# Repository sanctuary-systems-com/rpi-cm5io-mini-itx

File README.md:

# rpi-cm5io-mini-itx
A mini ITX board with PCIe x16 based on the Raspberry Pi Comput Module 5 IO board

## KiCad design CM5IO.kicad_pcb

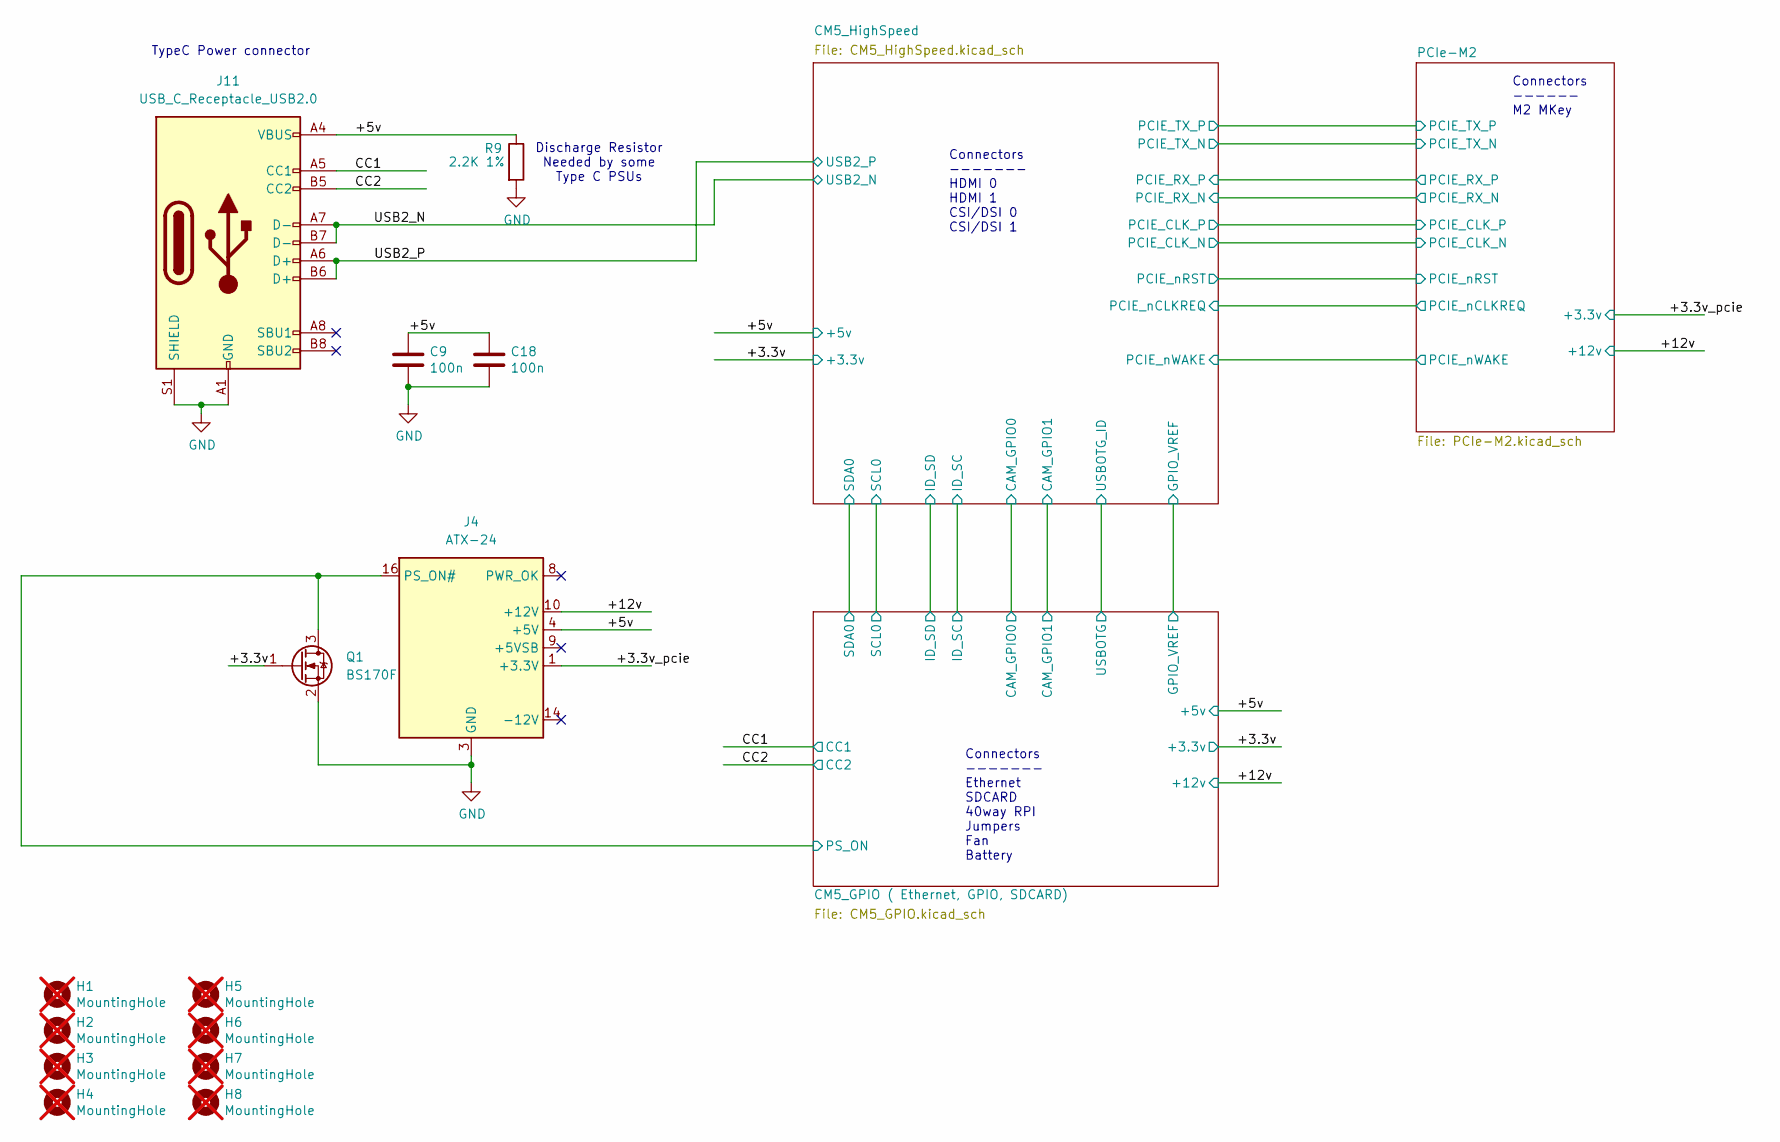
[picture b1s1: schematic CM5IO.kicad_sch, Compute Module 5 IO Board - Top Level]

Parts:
C9, C18: 100n; C_0402_1005Metric; Part Description 0.1uF 10% 16V Ceramic Capacitor X7R 040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; LCSC C92753
H1, H6, H7, H8: MountingHole; atx_mountinghole; Part Description M2.5 mounting hole; not fitted
H2, H3, H4, H5: MountingHole; MountingHole_2.7mm_M2.5_DIN965; Part Description M2.5 mounting hole; not fitted
J4: ATX-24; Molex_Mini-Fit_Jr_5566-24A_2x12_P4.20mm_Vertical; LCSC C114088
J11: USB_C_Receptacle_USB2.0; USB_C_Receptacle_GCT_USB4105-xx-A_16P_TopMnt_Horizontal; Part Description USBC USB2 data and power connector; LCSC C5184243
Q1: BS170F; SOT-23; LCSC C16197299
R9: 2.2K 1%; R_0402_1005Metric; Part Description Resistor 2.2K M1005 1% 63mW; LCSC C328314

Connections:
/+3.3v: Q1.1 (G); also elsewhere on the board
/+3.3v_pcie: J4.1 (+3.3V), J4.2 (+3.3V), J4.12 (+3.3V), J4.13 (+3.3V); also elsewhere on the board
/+5v: C9.1, C18.1, J4.4 (+5V), J4.6 (+5V), J4.21 (+5V), J4.22 (+5V), J4.23 (+5V), J11.A4 (VBUS), J11.A9 (VBUS), J11.B4 (VBUS), J11.B9 (VBUS), R9.1; also elsewhere on the board
/+12v: J4.10 (+12V), J4.11 (+12V); also elsewhere on the board
/CC1: J11.A5 (CC1); also elsewhere on the board
/CC2: J11.B5 (CC2); also elsewhere on the board
/CM5_GPIO ( Ethernet, GPIO, SDCARD)/PS_ON: J4.16 (PS_ON#), Q1.3 (D); also elsewhere on the board
/USB2_N: J11.A7 (D-), J11.B7 (D-); also elsewhere on the board
/USB2_P: J11.A6 (D+), J11.B6 (D+); also elsewhere on the board
GND: C9.2, C18.2, J4.3 (GND), J4.5 (GND), J4.7 (GND), J4.15 (GND), J4.17 (GND), J4.18 (GND), J4.19 (GND), J4.24 (GND), J11.A1 (GND), J11.A12 (GND), J11.B1 (GND), J11.B12 (GND), J11.S1 (SHIELD), Q1.2 (S), R9.2; also elsewhere on the board

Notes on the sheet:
Connectors ------- Ethernet SDCARD 40way RPI Jumpers Fan Battery
Connectors ------ M2 MKey
Discharge Resistor Needed by some Type C PSUs
TypeC Power connector
Connectors ------- HDMI 0 HDMI 1 CSI/DSI 0 CSI/DSI 1

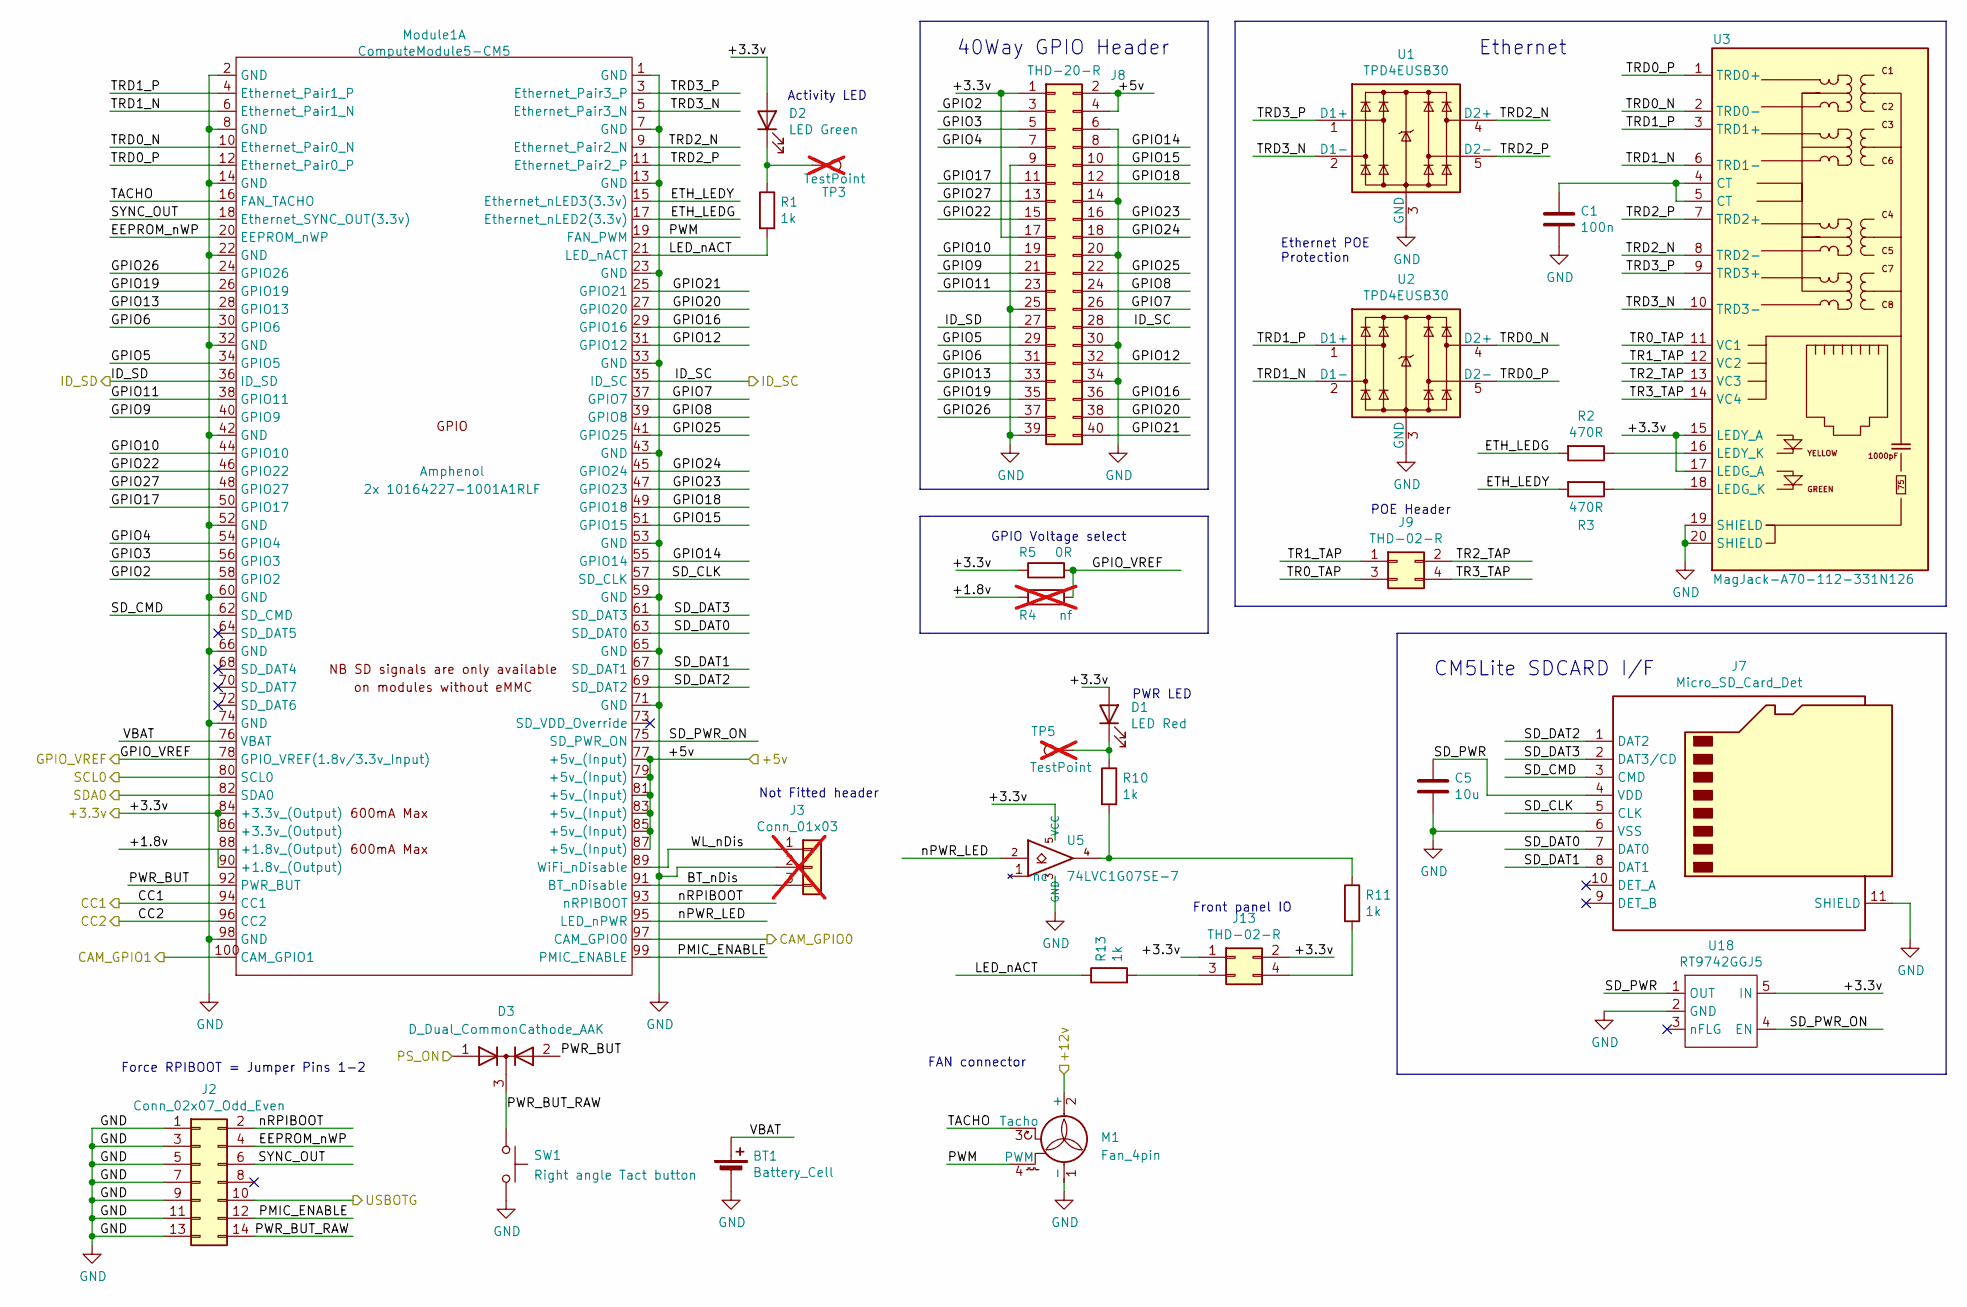
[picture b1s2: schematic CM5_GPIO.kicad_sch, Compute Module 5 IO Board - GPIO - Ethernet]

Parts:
BT1: Battery_Cell; BatteryHolder_Keystone_3034_1x20mm; Part Description Battery Retainer Coin, 20.0mm 1 Cell SM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; LCSC C5213768
C1: 100n; C_0402_1005Metric; Part Description 0.1uF 10% 16V Ceramic Capacitor X7R 040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; LCSC C92753
C5: 10u; C_0805_2012Metric; Part Description 10uF 10% 10V Ceramic Capacitor X7R 0805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; LCSC C117956
D1: LED Red; LED_0603_1608Metric; Part Description Red 620nm LED Indication - Discrete 2.2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; LCSC C125114
D2: LED Green; LED_0603_1608Metric; Part Description Green 572nm LED Indication - Discrete 2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; LCSC C125113
D3: D_Dual_CommonCathode_AAK; SOT-23; mpn BAT54-05; LCSC C37704
J2: Conn_02x07_Odd_Even; PinHeader_2x07_P2.54mm_Vertical; Part Description PinHeader_2x07_P2.54mm_Vertical; LCSC C492424
J3: Conn_01x03; PinHeader_1x03_P2.54mm_Vertical; Part Description 3pin 0.1" connector; not fitted
J7: Micro_SD_Card_Det; SDCARD_MOLEX_503398-1892; Part Description 9 (8 + 1) Position Card Connector micro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; LCSC C428492
J8: THD-20-R; PinHeader_2x20_P2.54mm_Vertical; Part Description PinHeader_2x20_P2.54mm_Vertical; LCSC C124383
J9, J13: THD-02-R; PinHeader_2x02_P2.54mm_Vertical; Part Description PinHeader_2x02_P2.54mm_Vertical; LCSC C492419
M1: Fan_4pin; FanPinHeader_1x04_P2.54mm_Vertical; mpn 0470531000; LCSC C240840
Module1: ComputeModule5-CM5; Raspberry-Pi-5-Compute-Module; Part Description 100 Position Connector Receptacle, Cent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; LCSC C19089295
R1, R10, R11, R13: 1k; R_0402_1005Metric; Part Description Resistor 1K M1005 1% 63mW; LCSC C131360
R2, R3: 470R; R_0402_1005Metric; Part Description Resistor 470R M1005 1% 63mW; LCSC C352415
R4: nf; R_0805_2012Metric_Pad1.20x1.40mm_HandSolder; not fitted
R5: 0R; R_0805_2012Metric_Pad1.20x1.40mm_HandSolder; Part Description Resistor 0R M2012 5%; LCSC C17477
SW1: Right angle Tact button; SW_Tactile_SPST_Angled_PTS645Vx58-2LFS; Part Description Right angle through hole Tact switch; LCSC C127680
TP3, TP5: TestPoint; TestPoint_Pad_2.0x2.0mm; Part Description Test point; not fitted
U1, U2: TPD4EUSB30; USON-10_2.5x1.0mm_P0.5mm; Part Description Quad TVS diode for high speed signals (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; LCSC C913227
U3: MagJack-A70-112-331N126; TRJG0926HENL; Part Description Gigabit Ethernet Magjack
U5: 74LVC1G07SE-7; SOT-353_SC-70-5; Part Description Buffer, Non-Inverting 1 Element 1 Bit p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; LCSC C67531
U18: RT9742GGJ5; SOT-23-5; Part Description Power Switch/Driver 1:1 N-Channel 1A TS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; LCSC C250547

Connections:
/+3.3v: D1.2 (A), D2.2 (A), J8.1, J8.17, J13.1, J13.2, Module1.84 (+3.3v_(Output)), Module1.86 (+3.3v_(Output)), R5.1, U3.15 (LEDY_A), U3.17 (LEDG_A), U5.5 (VCC), U18.5 (IN); also elsewhere on the board
/+5v: J8.2, J8.4, Module1.77 (+5v_(Input)), Module1.79 (+5v_(Input)), Module1.81 (+5v_(Input)), Module1.83 (+5v_(Input)), Module1.85 (+5v_(Input)), Module1.87 (+5v_(Input)); also elsewhere on the board
/+12v: M1.2 (+); also elsewhere on the board
/CC1: Module1.94 (CC1); also elsewhere on the board
/CC2: Module1.96 (CC2); also elsewhere on the board
/CM5_GPIO ( Ethernet, GPIO, SDCARD)/+1.8v: Module1.88 (+1.8v_(Output)), Module1.90 (+1.8v_(Output)), R4.1
/CM5_GPIO ( Ethernet, GPIO, SDCARD)/BT_nDis: J3.3, Module1.91 (BT_nDisable)
/CM5_GPIO ( Ethernet, GPIO, SDCARD)/CAM_GPIO0: Module1.97 (CAM_GPIO0); also elsewhere on the board
/CM5_GPIO ( Ethernet, GPIO, SDCARD)/CAM_GPIO1: Module1.100 (CAM_GPIO1); also elsewhere on the board
/CM5_GPIO ( Ethernet, GPIO, SDCARD)/EEPROM_nWP: J2.4, Module1.20 (EEPROM_nWP)
/CM5_GPIO ( Ethernet, GPIO, SDCARD)/ETH_LEDG: Module1.17 (Ethernet_nLED2(3.3v)), R2.2
/CM5_GPIO ( Ethernet, GPIO, SDCARD)/ETH_LEDY: Module1.15 (Ethernet_nLED3(3.3v)), R3.2
/CM5_GPIO ( Ethernet, GPIO, SDCARD)/GPIO2: J8.3, Module1.58 (GPIO2)
/CM5_GPIO ( Ethernet, GPIO, SDCARD)/GPIO3: J8.5, Module1.56 (GPIO3)
/CM5_GPIO ( Ethernet, GPIO, SDCARD)/GPIO4: J8.7, Module1.54 (GPIO4)
/CM5_GPIO ( Ethernet, GPIO, SDCARD)/GPIO5: J8.29, Module1.34 (GPIO5)
/CM5_GPIO ( Ethernet, GPIO, SDCARD)/GPIO6: J8.31, Module1.30 (GPIO6)
/CM5_GPIO ( Ethernet, GPIO, SDCARD)/GPIO7: J8.26, Module1.37 (GPIO7)
/CM5_GPIO ( Ethernet, GPIO, SDCARD)/GPIO8: J8.24, Module1.39 (GPIO8)
/CM5_GPIO ( Ethernet, GPIO, SDCARD)/GPIO9: J8.21, Module1.40 (GPIO9)
/CM5_GPIO ( Ethernet, GPIO, SDCARD)/GPIO10: J8.19, Module1.44 (GPIO10)
/CM5_GPIO ( Ethernet, GPIO, SDCARD)/GPIO11: J8.23, Module1.38 (GPIO11)
/CM5_GPIO ( Ethernet, GPIO, SDCARD)/GPIO12: J8.32, Module1.31 (GPIO12)
/CM5_GPIO ( Ethernet, GPIO, SDCARD)/GPIO13: J8.33, Module1.28 (GPIO13)
/CM5_GPIO ( Ethernet, GPIO, SDCARD)/GPIO14: J8.8, Module1.55 (GPIO14)
/CM5_GPIO ( Ethernet, GPIO, SDCARD)/GPIO15: J8.10, Module1.51 (GPIO15)
/CM5_GPIO ( Ethernet, GPIO, SDCARD)/GPIO16: J8.36, Module1.29 (GPIO16)
/CM5_GPIO ( Ethernet, GPIO, SDCARD)/GPIO17: J8.11, Module1.50 (GPIO17)
/CM5_GPIO ( Ethernet, GPIO, SDCARD)/GPIO18: J8.12, Module1.49 (GPIO18)
/CM5_GPIO ( Ethernet, GPIO, SDCARD)/GPIO19: J8.35, Module1.26 (GPIO19)
/CM5_GPIO ( Ethernet, GPIO, SDCARD)/GPIO20: J8.38, Module1.27 (GPIO20)
/CM5_GPIO ( Ethernet, GPIO, SDCARD)/GPIO21: J8.40, Module1.25 (GPIO21)
/CM5_GPIO ( Ethernet, GPIO, SDCARD)/GPIO22: J8.15, Module1.46 (GPIO22)
/CM5_GPIO ( Ethernet, GPIO, SDCARD)/GPIO23: J8.16, Module1.47 (GPIO23)
/CM5_GPIO ( Ethernet, GPIO, SDCARD)/GPIO24: J8.18, Module1.45 (GPIO24)
/CM5_GPIO ( Ethernet, GPIO, SDCARD)/GPIO25: J8.22, Module1.41 (GPIO25)
/CM5_GPIO ( Ethernet, GPIO, SDCARD)/GPIO26: J8.37, Module1.24 (GPIO26)
/CM5_GPIO ( Ethernet, GPIO, SDCARD)/GPIO27: J8.13, Module1.48 (GPIO27)
/CM5_GPIO ( Ethernet, GPIO, SDCARD)/GPIO_VREF: Module1.78 (GPIO_VREF(1.8v/3.3v_Input)), R4.2, R5.2; also elsewhere on the board
/CM5_GPIO ( Ethernet, GPIO, SDCARD)/ID_SC: J8.28, Module1.35 (ID_SC); also elsewhere on the board
/CM5_GPIO ( Ethernet, GPIO, SDCARD)/ID_SD: J8.27, Module1.36 (ID_SD); also elsewhere on the board
/CM5_GPIO ( Ethernet, GPIO, SDCARD)/LED_nACT: Module1.21 (LED_nACT), R1.2, R13.1
/CM5_GPIO ( Ethernet, GPIO, SDCARD)/PMIC_ENABLE: J2.12, Module1.99 (PMIC_ENABLE)
/CM5_GPIO ( Ethernet, GPIO, SDCARD)/PS_ON: D3.1 (A); also elsewhere on the board
/CM5_GPIO ( Ethernet, GPIO, SDCARD)/PWM: M1.4 (PWM), Module1.19 (FAN_PWM)
/CM5_GPIO ( Ethernet, GPIO, SDCARD)/PWR_BUT: D3.2 (A), Module1.92 (PWR_BUT)
/CM5_GPIO ( Ethernet, GPIO, SDCARD)/PWR_BUT_RAW: D3.3 (K), J2.14, SW1.1
/CM5_GPIO ( Ethernet, GPIO, SDCARD)/SD_CLK: J7.5 (CLK), Module1.57 (SD_CLK)
/CM5_GPIO ( Ethernet, GPIO, SDCARD)/SD_CMD: J7.3 (CMD), Module1.62 (SD_CMD)
/CM5_GPIO ( Ethernet, GPIO, SDCARD)/SD_DAT0: J7.7 (DAT0), Module1.63 (SD_DAT0)
/CM5_GPIO ( Ethernet, GPIO, SDCARD)/SD_DAT1: J7.8 (DAT1), Module1.67 (SD_DAT1)
/CM5_GPIO ( Ethernet, GPIO, SDCARD)/SD_DAT2: J7.1 (DAT2), Module1.69 (SD_DAT2)
/CM5_GPIO ( Ethernet, GPIO, SDCARD)/SD_DAT3: J7.2 (DAT3/CD), Module1.61 (SD_DAT3)
/CM5_GPIO ( Ethernet, GPIO, SDCARD)/SD_PWR: C5.1, J7.4 (VDD), U18.1 (OUT)
/CM5_GPIO ( Ethernet, GPIO, SDCARD)/SD_PWR_ON: Module1.75 (SD_PWR_ON), U18.4 (EN)
/CM5_GPIO ( Ethernet, GPIO, SDCARD)/SYNC_OUT: J2.6, Module1.18 (Ethernet_SYNC_OUT(3.3v))
/CM5_GPIO ( Ethernet, GPIO, SDCARD)/TACHO: M1.3 (Tacho), Module1.16 (FAN_TACHO)
/CM5_GPIO ( Ethernet, GPIO, SDCARD)/TR0_TAP: J9.3, U3.11 (VC1)
/CM5_GPIO ( Ethernet, GPIO, SDCARD)/TR1_TAP: J9.1, U3.12 (VC2)
/CM5_GPIO ( Ethernet, GPIO, SDCARD)/TR2_TAP: J9.2, U3.13 (VC3)
/CM5_GPIO ( Ethernet, GPIO, SDCARD)/TR3_TAP: J9.4, U3.14 (VC4)
/CM5_GPIO ( Ethernet, GPIO, SDCARD)/TRD0_N: Module1.10 (Ethernet_Pair0_N), U2.4 (D2+), U2.7, U3.2 (TRD0-)
/CM5_GPIO ( Ethernet, GPIO, SDCARD)/TRD0_P: Module1.12 (Ethernet_Pair0_P), U2.5 (D2-), U2.6, U3.1 (TRD0+)
/CM5_GPIO ( Ethernet, GPIO, SDCARD)/TRD1_N: Module1.6 (Ethernet_Pair1_N), U2.2 (D1-), U2.9, U3.6 (TRD1-)
/CM5_GPIO ( Ethernet, GPIO, SDCARD)/TRD1_P: Module1.4 (Ethernet_Pair1_P), U2.1 (D1+), U2.10, U3.3 (TRD1+)
/CM5_GPIO ( Ethernet, GPIO, SDCARD)/TRD2_N: Module1.9 (Ethernet_Pair2_N), U1.4 (D2+), U1.7, U3.8 (TRD2-)
/CM5_GPIO ( Ethernet, GPIO, SDCARD)/TRD2_P: Module1.11 (Ethernet_Pair2_P), U1.5 (D2-), U1.6, U3.7 (TRD2+)
/CM5_GPIO ( Ethernet, GPIO, SDCARD)/TRD3_N: Module1.5 (Ethernet_Pair3_N), U1.2 (D1-), U1.9, U3.10 (TRD3-)
/CM5_GPIO ( Ethernet, GPIO, SDCARD)/TRD3_P: Module1.3 (Ethernet_Pair3_P), U1.1 (D1+), U1.10, U3.9 (TRD3+)
/CM5_GPIO ( Ethernet, GPIO, SDCARD)/USBOTG: J2.10; also elsewhere on the board
/CM5_GPIO ( Ethernet, GPIO, SDCARD)/VBAT: BT1.1 (+), Module1.76 (VBAT)
/CM5_GPIO ( Ethernet, GPIO, SDCARD)/WL_nDis: J3.1, Module1.89 (WiFi_nDisable)
/CM5_GPIO ( Ethernet, GPIO, SDCARD)/nPWR_LED: Module1.95 (LED_nPWR), U5.2
/CM5_GPIO ( Ethernet, GPIO, SDCARD)/nRPIBOOT: J2.2, Module1.93 (nRPIBOOT)
/CM5_HighSpeed/SCL0: Module1.80 (SCL0); also elsewhere on the board
/CM5_HighSpeed/SDA0: Module1.82 (SDA0); also elsewhere on the board
GND: BT1.2 (-), C1.2, C5.2, J2.1, J2.3, J2.5, J2.7, J2.9, J2.11, J2.13, J3.2, J7.6 (VSS), J7.11 (SHIELD), J8.6, J8.9, J8.14, J8.20, J8.25, J8.30, J8.34, J8.39, M1.1 (-), Module1.1 (GND), Module1.2 (GND), Module1.7 (GND), Module1.8 (GND), Module1.13 (GND), Module1.14 (GND), Module1.22 (GND), Module1.23 (GND), Module1.32 (GND), Module1.33 (GND), Module1.42 (GND), Module1.43 (GND), Module1.52 (GND), Module1.53 (GND), Module1.59 (GND), Module1.60 (GND), Module1.65 (GND), Module1.66 (GND), Module1.71 (GND), Module1.74 (GND), Module1.98 (GND), SW1.2, U1.3 (GND), U1.8 (GND), U2.3 (GND), U2.8 (GND), U3.19 (SHIELD), U3.20 (SHIELD), U5.3 (GND), U18.2 (GND); also elsewhere on the board
unnamed: C1.1, U3.4 (CT), U3.5 (CT)
unnamed: D1.1 (K), R10.1, TP5.1
unnamed: D2.1 (K), R1.1, TP3.1
unnamed: J13.3, R13.2
unnamed: J13.4, R11.2
unnamed: R10.2, R11.1, U5.4
unnamed: R3.1, U3.18 (LEDG_K)
unnamed: R2.1, U3.16 (LEDY_K)

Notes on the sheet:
40Way GPIO Header
Activity LED
FAN connector
Ethernet POE Protection
Front panel IO
GPIO Voltage select
Not Fitted header
POE Header
Force RPIBOOT = Jumper Pins 1-2
PWR LED
Ethernet
CM5Lite SDCARD I/F

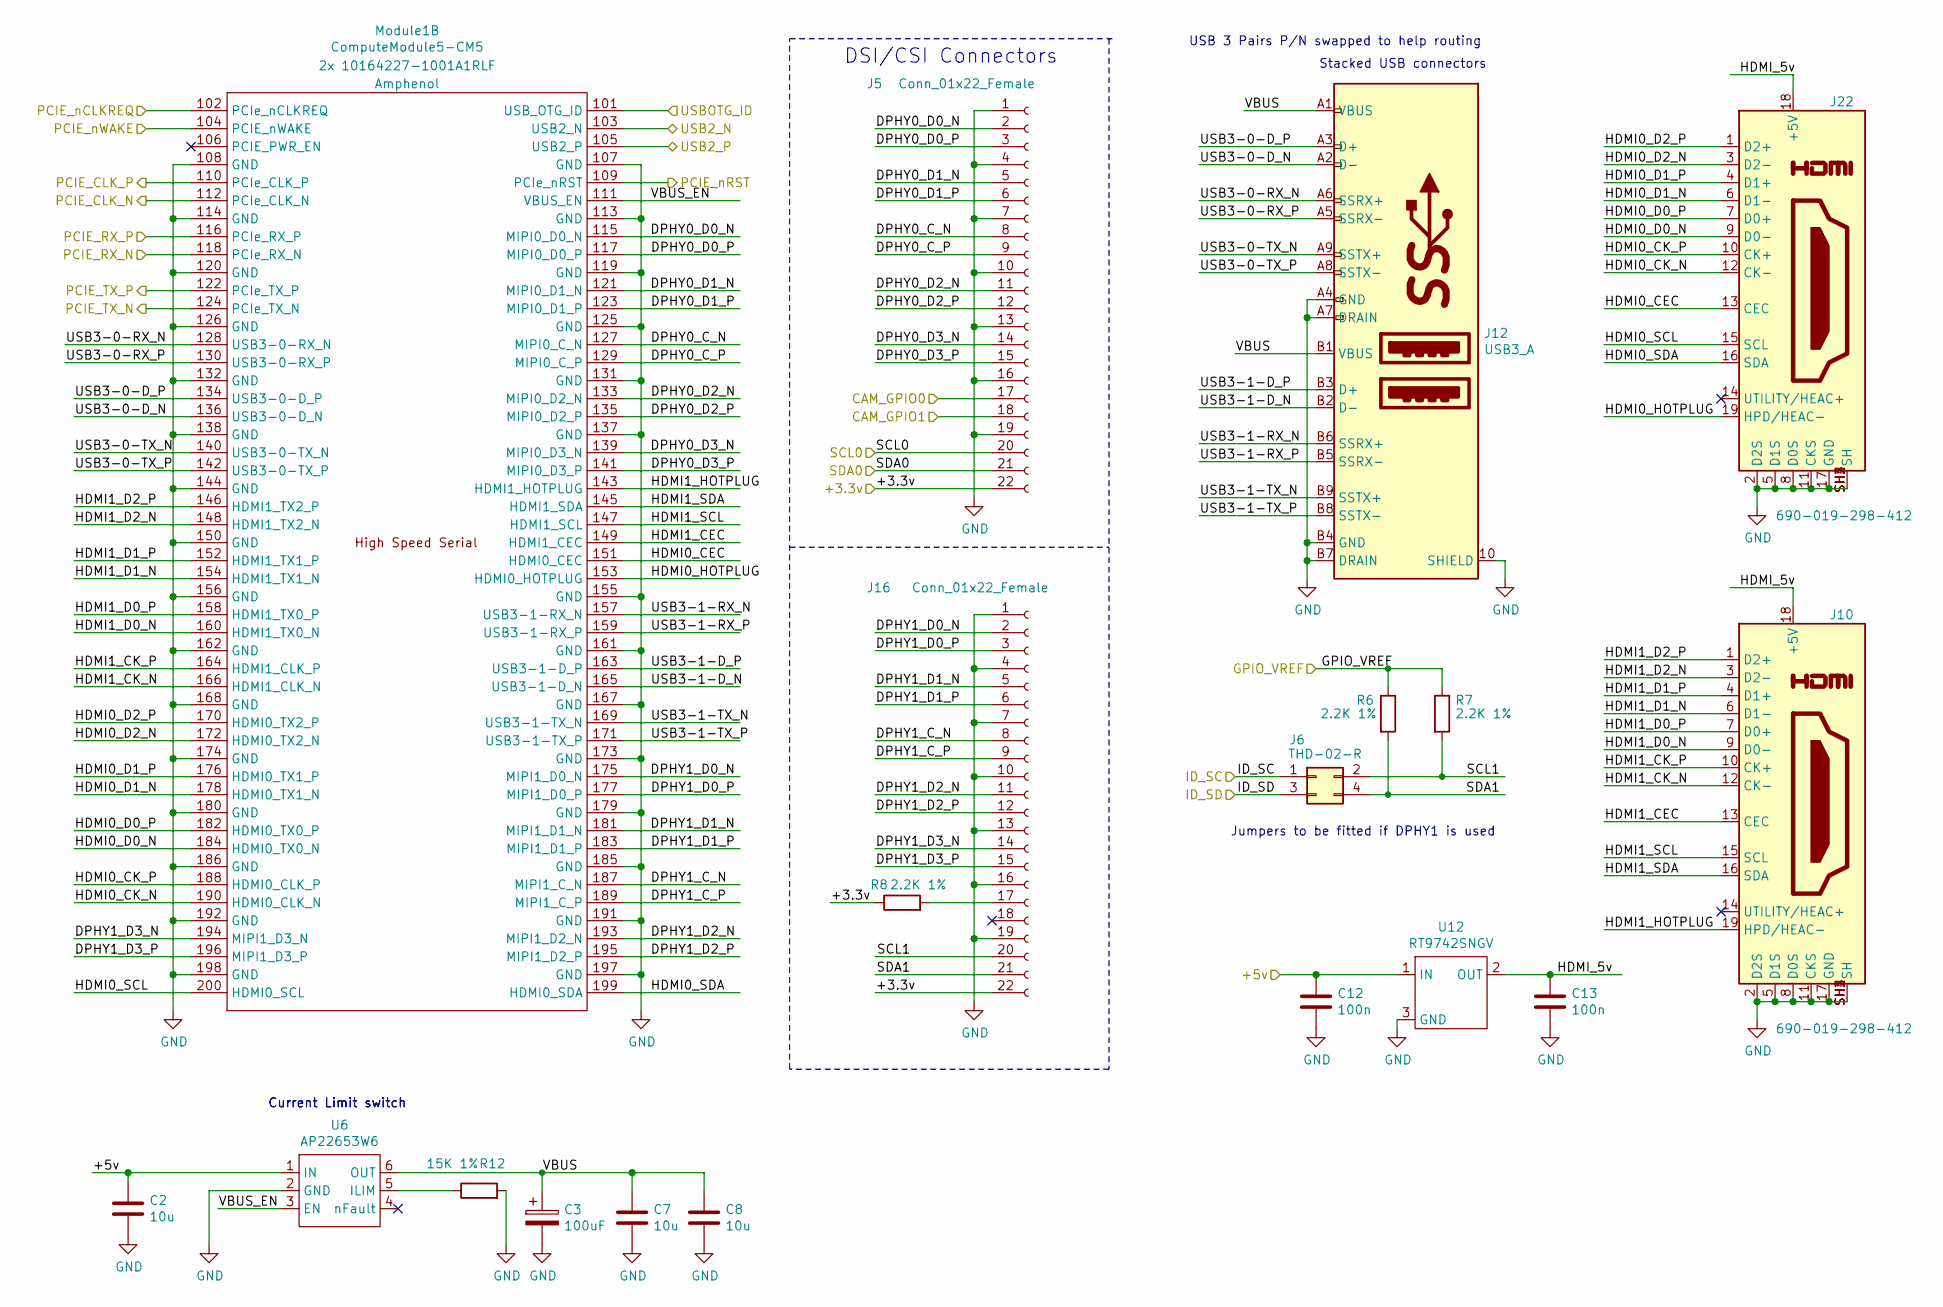
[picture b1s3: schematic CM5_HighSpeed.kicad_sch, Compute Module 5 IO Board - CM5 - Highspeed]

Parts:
C2, C7, C8: 10u; C_0805_2012Metric; Part Description 10uF 10% 10V Ceramic Capacitor X7R 0805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; LCSC C117956
C3: 100uF; CP_EIA-7343-31_Kemet-D; Part Description Capacitor, SP-Cap, 100u, 6.3V, 15mR ESR; LCSC C189619
C12, C13: 100n; C_0402_1005Metric; Part Description 0.1uF 10% 16V Ceramic Capacitor X7R 040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; LCSC C92753
J5, J16: Conn_01x22_Female; Hirose_FH12-22S-0.5SH_1x22-1MP_P0.50mm_Horizontal; Part Description 22 Position FFC, FPC Connector Contacts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; LCSC C597981
J6: THD-02-R; PinHeader_2x02_P2.54mm_Vertical; Part Description PinHeader_2x02_P2.54mm_Vertical; LCSC C492419
J10, J22: 690-019-298-412; EDAC 690-019-298-412; Part Description HDMI Connector, Right Angle, 19 Contact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; LCSC C720616
J12: USB3_A; MTCONN_UBAF30-D2011; Part Description Dual USB 3 connector; LCSC C5519092
Module1: ComputeModule5-CM5; Raspberry-Pi-5-Compute-Module; Part Description 100 Position Connector Receptacle, Cent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; LCSC C19089295
R6, R7, R8: 2.2K 1%; R_0402_1005Metric; Part Description Resistor 2.2K M1005 1% 63mW; LCSC C328314
R12: 15K 1%; R_0402_1005Metric; Part Description Resistor 15K M1005 1% 63mW; LCSC C525579
U6: AP22653W6; SOT-23-6; Part Description Power Switch/Driver 1:1 P-Channel 2.1A 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; LCSC C2158037
U12: RT9742SNGV; TSOT-23_HandSoldering; Part Description Power Switch/Driver 1:1 N-Channel 500mA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; LCSC C3235509

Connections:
/+3.3v: J5.22, J16.22, R8.1; also elsewhere on the board
/+5v: C2.1, C12.1, U6.1 (IN), U12.1 (IN); also elsewhere on the board
/CM5_GPIO ( Ethernet, GPIO, SDCARD)/CAM_GPIO0: J5.17; also elsewhere on the board
/CM5_GPIO ( Ethernet, GPIO, SDCARD)/CAM_GPIO1: J5.18; also elsewhere on the board
/CM5_GPIO ( Ethernet, GPIO, SDCARD)/GPIO_VREF: R6.1, R7.1; also elsewhere on the board
/CM5_GPIO ( Ethernet, GPIO, SDCARD)/ID_SC: J6.1; also elsewhere on the board
/CM5_GPIO ( Ethernet, GPIO, SDCARD)/ID_SD: J6.3; also elsewhere on the board
/CM5_GPIO ( Ethernet, GPIO, SDCARD)/USBOTG: Module1.101 (USB_OTG_ID); also elsewhere on the board
/CM5_HighSpeed/DPHY0_C_N: J5.8, Module1.127 (MIPI0_C_N)
/CM5_HighSpeed/DPHY0_C_P: J5.9, Module1.129 (MIPI0_C_P)
/CM5_HighSpeed/DPHY0_D0_N: J5.2, Module1.115 (MIPI0_D0_N)
/CM5_HighSpeed/DPHY0_D0_P: J5.3, Module1.117 (MIPI0_D0_P)
/CM5_HighSpeed/DPHY0_D1_N: J5.5, Module1.121 (MIPI0_D1_N)
/CM5_HighSpeed/DPHY0_D1_P: J5.6, Module1.123 (MIPI0_D1_P)
/CM5_HighSpeed/DPHY0_D2_N: J5.11, Module1.133 (MIPI0_D2_N)
/CM5_HighSpeed/DPHY0_D2_P: J5.12, Module1.135 (MIPI0_D2_P)
/CM5_HighSpeed/DPHY0_D3_N: J5.14, Module1.139 (MIPI0_D3_N)
/CM5_HighSpeed/DPHY0_D3_P: J5.15, Module1.141 (MIPI0_D3_P)
/CM5_HighSpeed/DPHY1_C_N: J16.8, Module1.187 (MIPI1_C_N)
/CM5_HighSpeed/DPHY1_C_P: J16.9, Module1.189 (MIPI1_C_P)
/CM5_HighSpeed/DPHY1_D0_N: J16.2, Module1.175 (MIPI1_D0_N)
/CM5_HighSpeed/DPHY1_D0_P: J16.3, Module1.177 (MIPI1_D0_P)
/CM5_HighSpeed/DPHY1_D1_N: J16.5, Module1.181 (MIPI1_D1_N)
/CM5_HighSpeed/DPHY1_D1_P: J16.6, Module1.183 (MIPI1_D1_P)
/CM5_HighSpeed/DPHY1_D2_N: J16.11, Module1.193 (MIPI1_D2_N)
/CM5_HighSpeed/DPHY1_D2_P: J16.12, Module1.195 (MIPI1_D2_P)
/CM5_HighSpeed/DPHY1_D3_N: J16.14, Module1.194 (MIPI1_D3_N)
/CM5_HighSpeed/DPHY1_D3_P: J16.15, Module1.196 (MIPI1_D3_P)
/CM5_HighSpeed/HDMI0_CEC: J22.13 (CEC), Module1.151 (HDMI0_CEC)
/CM5_HighSpeed/HDMI0_CK_N: J22.12 (CK-), Module1.190 (HDMI0_CLK_N)
/CM5_HighSpeed/HDMI0_CK_P: J22.10 (CK+), Module1.188 (HDMI0_CLK_P)
/CM5_HighSpeed/HDMI0_D0_N: J22.9 (D0-), Module1.184 (HDMI0_TX0_N)
/CM5_HighSpeed/HDMI0_D0_P: J22.7 (D0+), Module1.182 (HDMI0_TX0_P)
/CM5_HighSpeed/HDMI0_D1_N: J22.6 (D1-), Module1.178 (HDMI0_TX1_N)
/CM5_HighSpeed/HDMI0_D1_P: J22.4 (D1+), Module1.176 (HDMI0_TX1_P)
/CM5_HighSpeed/HDMI0_D2_N: J22.3 (D2-), Module1.172 (HDMI0_TX2_N)
/CM5_HighSpeed/HDMI0_D2_P: J22.1 (D2+), Module1.170 (HDMI0_TX2_P)
/CM5_HighSpeed/HDMI0_HOTPLUG: J22.19 (HPD/HEAC-), Module1.153 (HDMI0_HOTPLUG)
/CM5_HighSpeed/HDMI0_SCL: J22.15 (SCL), Module1.200 (HDMI0_SCL)
/CM5_HighSpeed/HDMI0_SDA: J22.16 (SDA), Module1.199 (HDMI0_SDA)
/CM5_HighSpeed/HDMI1_CEC: J10.13 (CEC), Module1.149 (HDMI1_CEC)
/CM5_HighSpeed/HDMI1_CK_N: J10.12 (CK-), Module1.166 (HDMI1_CLK_N)
/CM5_HighSpeed/HDMI1_CK_P: J10.10 (CK+), Module1.164 (HDMI1_CLK_P)
/CM5_HighSpeed/HDMI1_D0_N: J10.9 (D0-), Module1.160 (HDMI1_TX0_N)
/CM5_HighSpeed/HDMI1_D0_P: J10.7 (D0+), Module1.158 (HDMI1_TX0_P)
/CM5_HighSpeed/HDMI1_D1_N: J10.6 (D1-), Module1.154 (HDMI1_TX1_N)
/CM5_HighSpeed/HDMI1_D1_P: J10.4 (D1+), Module1.152 (HDMI1_TX1_P)
/CM5_HighSpeed/HDMI1_D2_N: J10.3 (D2-), Module1.148 (HDMI1_TX2_N)
/CM5_HighSpeed/HDMI1_D2_P: J10.1 (D2+), Module1.146 (HDMI1_TX2_P)
/CM5_HighSpeed/HDMI1_HOTPLUG: J10.19 (HPD/HEAC-), Module1.143 (HDMI1_HOTPLUG)
/CM5_HighSpeed/HDMI1_SCL: J10.15 (SCL), Module1.147 (HDMI1_SCL)
/CM5_HighSpeed/HDMI1_SDA: J10.16 (SDA), Module1.145 (HDMI1_SDA)
/CM5_HighSpeed/HDMI_5v: C13.1, J10.18 (+5V), J22.18 (+5V), U12.2 (OUT)
/CM5_HighSpeed/PCIE_CLK_N: Module1.112 (PCIe_CLK_N); also elsewhere on the board
/CM5_HighSpeed/PCIE_CLK_P: Module1.110 (PCIe_CLK_P); also elsewhere on the board
/CM5_HighSpeed/PCIE_RX_N: Module1.118 (PCIe_RX_N); also elsewhere on the board
/CM5_HighSpeed/PCIE_RX_P: Module1.116 (PCIe_RX_P); also elsewhere on the board
/CM5_HighSpeed/PCIE_TX_N: Module1.124 (PCIe_TX_N); also elsewhere on the board
/CM5_HighSpeed/PCIE_TX_P: Module1.122 (PCIe_TX_P); also elsewhere on the board
/CM5_HighSpeed/PCIE_nCLKREQ: Module1.102 (PCIe_nCLKREQ); also elsewhere on the board
/CM5_HighSpeed/PCIE_nRST: Module1.109 (PCIe_nRST); also elsewhere on the board
/CM5_HighSpeed/PCIE_nWAKE: Module1.104 (PCIE_nWAKE); also elsewhere on the board
/CM5_HighSpeed/SCL0: J5.20; also elsewhere on the board
/CM5_HighSpeed/SCL1: J6.2, J16.20, R7.2
/CM5_HighSpeed/SDA0: J5.21; also elsewhere on the board
/CM5_HighSpeed/SDA1: J6.4, J16.21, R6.2
/CM5_HighSpeed/USB3-0-D_N: J12.A2 (D-), Module1.136 (USB3-0-D_N)
/CM5_HighSpeed/USB3-0-D_P: J12.A3 (D+), Module1.134 (USB3-0-D_P)
/CM5_HighSpeed/USB3-0-RX_N: J12.A6 (SSRX+), Module1.128 (USB3-0-RX_N)
/CM5_HighSpeed/USB3-0-RX_P: J12.A5 (SSRX-), Module1.130 (USB3-0-RX_P)
/CM5_HighSpeed/USB3-0-TX_N: J12.A9 (SSTX+), Module1.140 (USB3-0-TX_N)
/CM5_HighSpeed/USB3-0-TX_P: J12.A8 (SSTX-), Module1.142 (USB3-0-TX_P)
/CM5_HighSpeed/USB3-1-D_N: J12.B2 (D-), Module1.165 (USB3-1-D_N)
/CM5_HighSpeed/USB3-1-D_P: J12.B3 (D+), Module1.163 (USB3-1-D_P)
/CM5_HighSpeed/USB3-1-RX_N: J12.B6 (SSRX+), Module1.157 (USB3-1-RX_N)
/CM5_HighSpeed/USB3-1-RX_P: J12.B5 (SSRX-), Module1.159 (USB3-1-RX_P)
/CM5_HighSpeed/USB3-1-TX_N: J12.B9 (SSTX+), Module1.169 (USB3-1-TX_N)
/CM5_HighSpeed/USB3-1-TX_P: J12.B8 (SSTX-), Module1.171 (USB3-1-TX_P)
/CM5_HighSpeed/VBUS: C3.1, C7.1, C8.1, J12.A1 (VBUS), J12.B1 (VBUS), U6.6 (OUT)
/CM5_HighSpeed/VBUS_EN: Module1.111 (VBUS_EN), U6.3 (EN)
/USB2_N: Module1.103 (USB2_N); also elsewhere on the board
/USB2_P: Module1.105 (USB2_P); also elsewhere on the board
GND: C2.2, C3.2, C7.2, C8.2, C12.2, C13.2, J5.1, J5.4, J5.7, J5.10, J5.13, J5.16, J5.19, J10.2 (D2S), J10.5 (D1S), J10.8 (D0S), J10.11 (CKS), J10.17 (GND), J10.SH1 (SH), J10.SH2 (SH), J10.SH3 (SH), J10.SH4 (SH), J12.10 (SHIELD), J12.A4 (GND), J12.A7 (DRAIN), J12.B4 (GND), J12.B7 (DRAIN), J16.1, J16.4, J16.7, J16.10, J16.13, J16.16, J16.19, J22.2 (D2S), J22.5 (D1S), J22.8 (D0S), J22.11 (CKS), J22.17 (GND), J22.SH1 (SH), J22.SH2 (SH), J22.SH3 (SH), J22.SH4 (SH), Module1.107 (GND), Module1.108 (GND), Module1.113 (GND), Module1.114 (GND), Module1.119 (GND), Module1.120 (GND), Module1.125 (GND), Module1.126 (GND), Module1.131 (GND), Module1.132 (GND), Module1.137 (GND), Module1.138 (GND), Module1.144 (GND), Module1.150 (GND), Module1.155 (GND), Module1.156 (GND), Module1.161 (GND), Module1.162 (GND), Module1.167 (GND), Module1.168 (GND), Module1.173 (GND), Module1.174 (GND), Module1.179 (GND), Module1.180 (GND), Module1.185 (GND), Module1.186 (GND), Module1.191 (GND), Module1.192 (GND), Module1.197 (GND), Module1.198 (GND), R12.2, U6.2 (GND), U12.3 (GND); also elsewhere on the board
unnamed: J16.17, R8.2
unnamed: R12.1, U6.5 (ILIM)

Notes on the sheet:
USB 3 Pairs P/N swapped to help routing
Jumpers to be fitted if DPHY1 is used
Current Limit switch
DSI/CSI Connectors
Stacked USB connectors

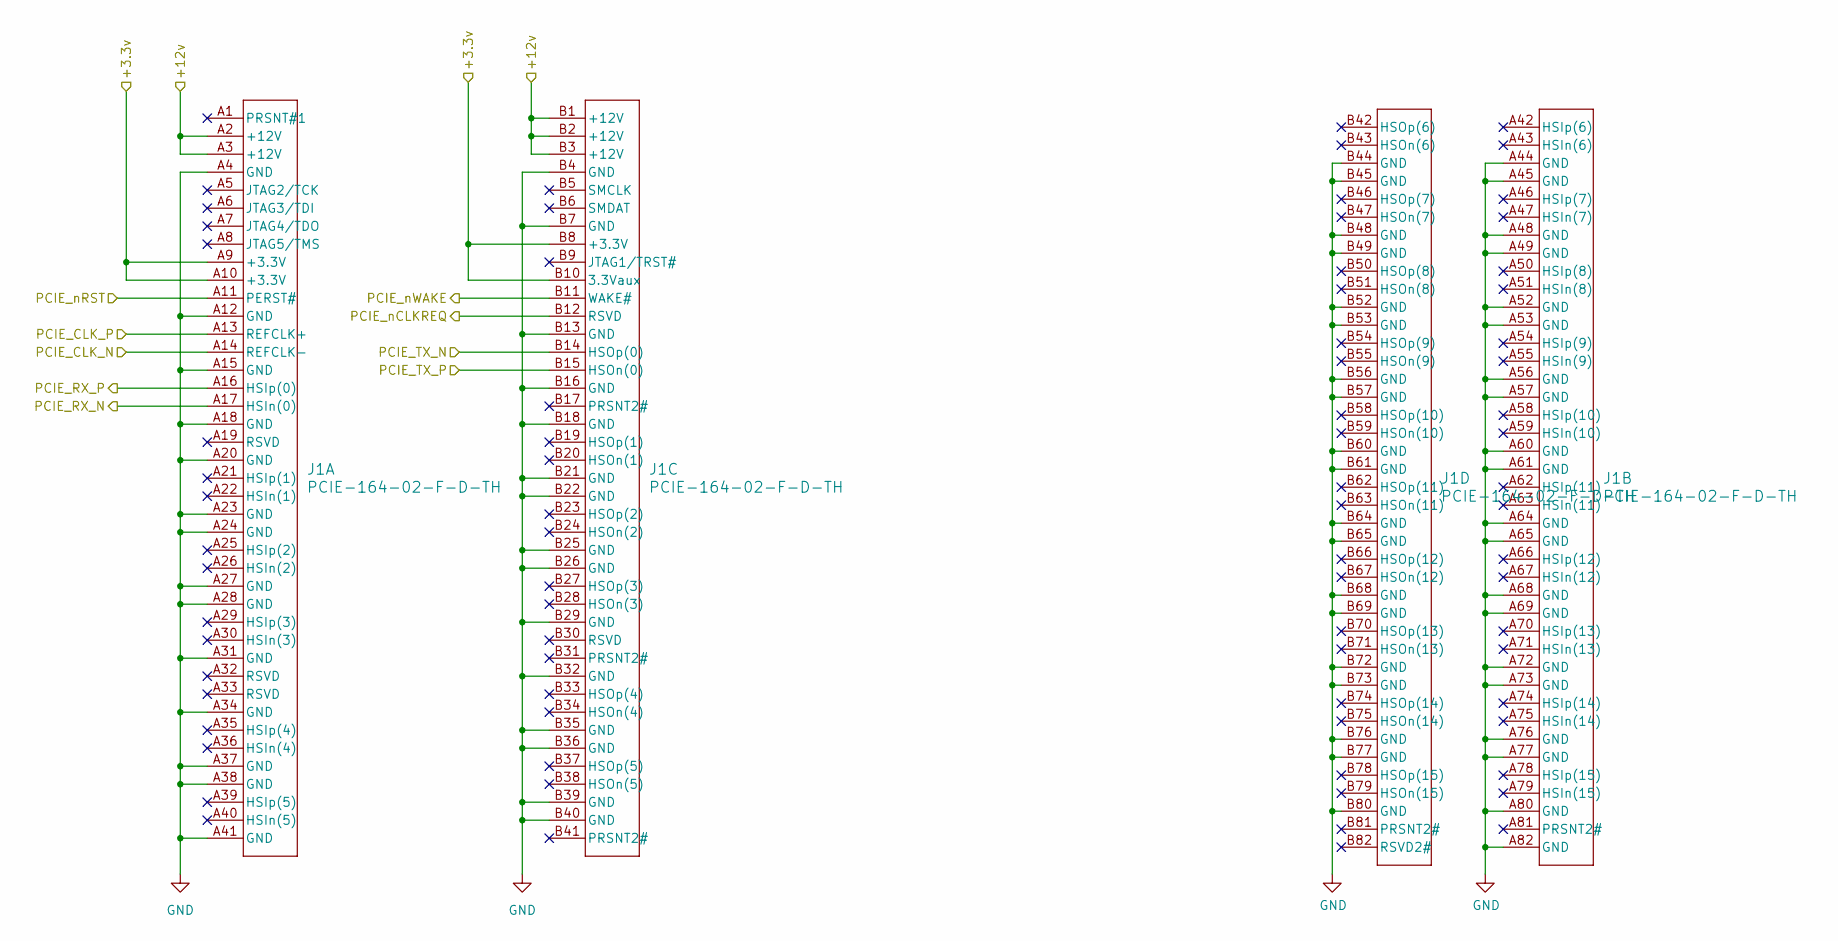
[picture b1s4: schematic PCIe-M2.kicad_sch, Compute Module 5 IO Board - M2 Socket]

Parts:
J1: PCIE-164-02-F-D-TH; CONN_PCIE-164-02-x-D-TH_SAI; LCSC C404112

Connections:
/+3.3v_pcie: J1.A9 (+3.3V), J1.A10 (+3.3V), J1.B8 (+3.3V), J1.B10 (3.3Vaux); also elsewhere on the board
/+12v: J1.A2 (+12V), J1.A3 (+12V), J1.B1 (+12V), J1.B2 (+12V), J1.B3 (+12V); also elsewhere on the board
/CM5_HighSpeed/PCIE_CLK_N: J1.A14 (REFCLK-); also elsewhere on the board
/CM5_HighSpeed/PCIE_CLK_P: J1.A13 (REFCLK+); also elsewhere on the board
/CM5_HighSpeed/PCIE_RX_N: J1.A17 (HSIn(0)); also elsewhere on the board
/CM5_HighSpeed/PCIE_RX_P: J1.A16 (HSIp(0)); also elsewhere on the board
/CM5_HighSpeed/PCIE_TX_N: J1.B14 (HSOp(0)); also elsewhere on the board
/CM5_HighSpeed/PCIE_TX_P: J1.B15 (HSOn(0)); also elsewhere on the board
/CM5_HighSpeed/PCIE_nCLKREQ: J1.B12 (RSVD); also elsewhere on the board
/CM5_HighSpeed/PCIE_nRST: J1.A11 (PERST#); also elsewhere on the board
/CM5_HighSpeed/PCIE_nWAKE: J1.B11 (WAKE#); also elsewhere on the board
GND: J1.A4 (GND), J1.A12 (GND), J1.A15 (GND), J1.A18 (GND), J1.A20 (GND), J1.A23 (GND), J1.A24 (GND), J1.A27 (GND), J1.A28 (GND), J1.A31 (GND), J1.A34 (GND), J1.A37 (GND), J1.A38 (GND), J1.A41 (GND), J1.A44 (GND), J1.A45 (GND), J1.A48 (GND), J1.A49 (GND), J1.A52 (GND), J1.A53 (GND), J1.A56 (GND), J1.A57 (GND), J1.A60 (GND), J1.A61 (GND), J1.A64 (GND), J1.A65 (GND), J1.A68 (GND), J1.A69 (GND), J1.A72 (GND), J1.A73 (GND), J1.A76 (GND), J1.A77 (GND), J1.A80 (GND), J1.A82 (GND), J1.B4 (GND), J1.B7 (GND), J1.B13 (GND), J1.B16 (GND), J1.B18 (GND), J1.B21 (GND), J1.B22 (GND), J1.B25 (GND), J1.B26 (GND), J1.B29 (GND), J1.B32 (GND), J1.B35 (GND), J1.B36 (GND), J1.B39 (GND), J1.B40 (GND), J1.B44 (GND), J1.B45 (GND), J1.B48 (GND), J1.B49 (GND), J1.B52 (GND), J1.B53 (GND), J1.B56 (GND), J1.B57 (GND), J1.B60 (GND), J1.B61 (GND), J1.B64 (GND), J1.B65 (GND), J1.B68 (GND), J1.B69 (GND), J1.B72 (GND), J1.B73 (GND), J1.B76 (GND), J1.B77 (GND), J1.B80 (GND); also elsewhere on the board

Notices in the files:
CM5IO.kicad_sch:
Copyright © 2024 Raspberry Pi Ltd.
